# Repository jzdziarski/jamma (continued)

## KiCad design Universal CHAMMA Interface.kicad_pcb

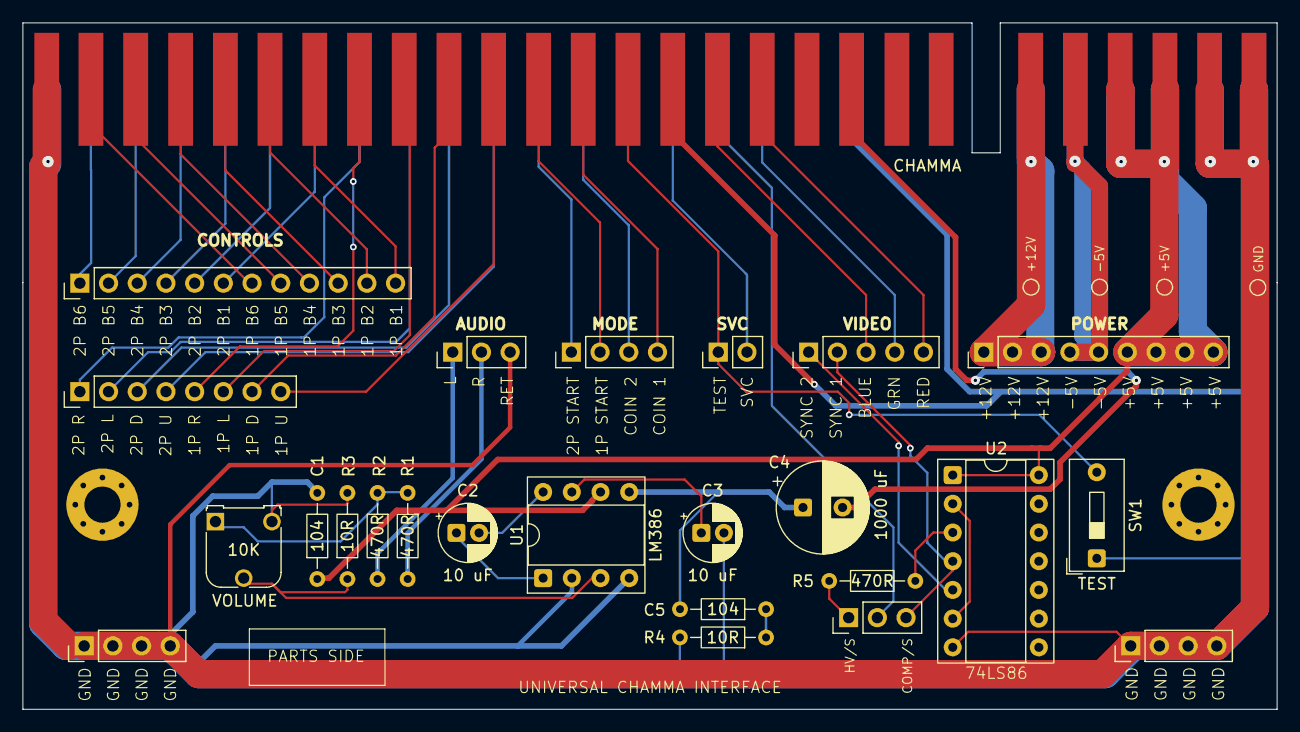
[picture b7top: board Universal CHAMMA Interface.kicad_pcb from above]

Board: 2 copper layers, 111.0 x 60.8 mm, 29 parts (0 on the bottom side), 49 nets.

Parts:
+5V, +12V: TestPoint_Pad_D1.0mm
-5V: TestPoint_Pad_D1.0mm
AUDIO: PinHeader_1x03_P2.54mm_Vertical
C1, C5: 104; R_Axial_DIN0204_L3.6mm_D1.6mm_P7.62mm_Horizontal
C2, C3: 10 uF; CP_Radial_D5.0mm_P2.00mm
C4: 1000 uF; CP_Radial_D8.0mm_P3.50mm
CHAMMA: HDR_JAMMA_56P_EDGE_CONNECTOR
CONTROLS: PinHeader_1x12_P2.54mm_Vertical
DIRECTIONALS: PinHeader_1x08_P2.54mm_Vertical
GND: TestPoint_Pad_D1.0mm
Ground: PinHeader_1x04_P2.54mm_Vertical
Ground#2: PinHeader_1x04_P2.54mm_Vertical
HV/S: PinHeader_1x03_P2.54mm_Vertical
MODE: PinHeader_1x04_P2.54mm_Vertical
POWER: PinHeader_1x09_P2.54mm_Vertical
R1, R2, R5: 470R; R_Axial_DIN0204_L3.6mm_D1.6mm_P7.62mm_Horizontal
R3, R4: 10R; R_Axial_DIN0204_L3.6mm_D1.6mm_P7.62mm_Horizontal
SVC: PinHeader_1x02_P2.54mm_Vertical
TEST: SW1; SW_DIP_SPSTx01_Slide_9.78x4.72mm_W7.62mm_P2.54mm
U1: LM386; DIP-8_W7.62mm_Socket
U2: DIP-14_W7.62mm_Socket
VIDEO: PinHeader_1x05_P2.54mm_Vertical
VOLUME: 10K; Potentiometer_Runtron_RM-065_Vertical

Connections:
1P_B1: CHAMMA.22, CONTROLS.12
1P_B2: CHAMMA.23, CONTROLS.11
1P_B3: CHAMMA.24, CONTROLS.10
1P_B4: CHAMMA.25, CONTROLS.9
1P_B5: CHAMMA.26, CONTROLS.8
1P_B6: CHAMMA.27, CONTROLS.7
1P_D: CHAMMA.19, DIRECTIONALS.7
1P_L: CHAMMA.20, DIRECTIONALS.6
1P_R: CHAMMA.21, DIRECTIONALS.5
1P_START: CHAMMA.17, MODE.2
1P_U: CHAMMA.18, DIRECTIONALS.8
2P_B1: CHAMMA.Z, CONTROLS.6
2P_B2: CHAMMA.a, CONTROLS.5
2P_B3: CHAMMA.b, CONTROLS.4
2P_B4: CHAMMA.c, CONTROLS.3
2P_B5: CHAMMA.d, CONTROLS.2
2P_B6: CHAMMA.e, CONTROLS.1
2P_D: CHAMMA.W, DIRECTIONALS.3
2P_L: CHAMMA.X, DIRECTIONALS.2
2P_R: CHAMMA.Y, DIRECTIONALS.1
2P_START: CHAMMA.U, MODE.1
2P_U: CHAMMA.V, DIRECTIONALS.4
+5V: +5V.1, C1.1, CHAMMA.3, CHAMMA.4, CHAMMA.C, CHAMMA.D, POWER.6, POWER.7, POWER.8, POWER.9, U1.6, U2.1, U2.14
+12V: +12V.1, CHAMMA.6, CHAMMA.F, POWER.1, POWER.2, POWER.3
-5V: -5V.1, CHAMMA.5, CHAMMA.E, POWER.4, POWER.5
AUDIO_L: AUDIO.1, R2.2
AUDIO_MONO: R1.1, R2.1, VOLUME.1
AUDIO_R: AUDIO.2, R1.2
C5_R4: C5.1, R4.1
COIN_1: CHAMMA.16, MODE.4
COIN_2: CHAMMA.T, MODE.3
GND: AUDIO.3, C1.2, C3.2, CHAMMA.1, CHAMMA.2, CHAMMA.14, CHAMMA.28, CHAMMA.A, CHAMMA.B, CHAMMA.L, CHAMMA.f, GND.1, Ground.1, Ground.2, Ground.3, Ground.4, Ground#2.1, Ground#2.2, Ground#2.3, Ground#2.4, R3.2, R4.2, TEST.1, U1.2, U1.4, U2.7, VOLUME.3
PREAMP: R3.1, U1.3, VOLUME.2
PREAMP_OUT: C4.1, C5.2, U1.5
SERVICE: CHAMMA.R, SVC.2
SPKR+: C4.2, CHAMMA.10
TEST: CHAMMA.15, SVC.1, TEST.2
U4_BYPASS: C3.1, U1.7
U4_GAIN_P1: C2.1, U1.1
U4_GAIN_P8: C2.2, U1.8
VID_B: CHAMMA.13, VIDEO.3
VID_CSYNC: CHAMMA.P, HV/S.2
VID_G: CHAMMA.N, VIDEO.4
VID_NXOR: HV/S.1, R5.1
VID_NXOR_R5: R5.2, U2.3
VID_R: CHAMMA.12, VIDEO.5
VID_SYN1: HV/S.3, U2.4, VIDEO.2
VID_SYN2: U2.5, VIDEO.1
VID_XOR: U2.2, U2.6

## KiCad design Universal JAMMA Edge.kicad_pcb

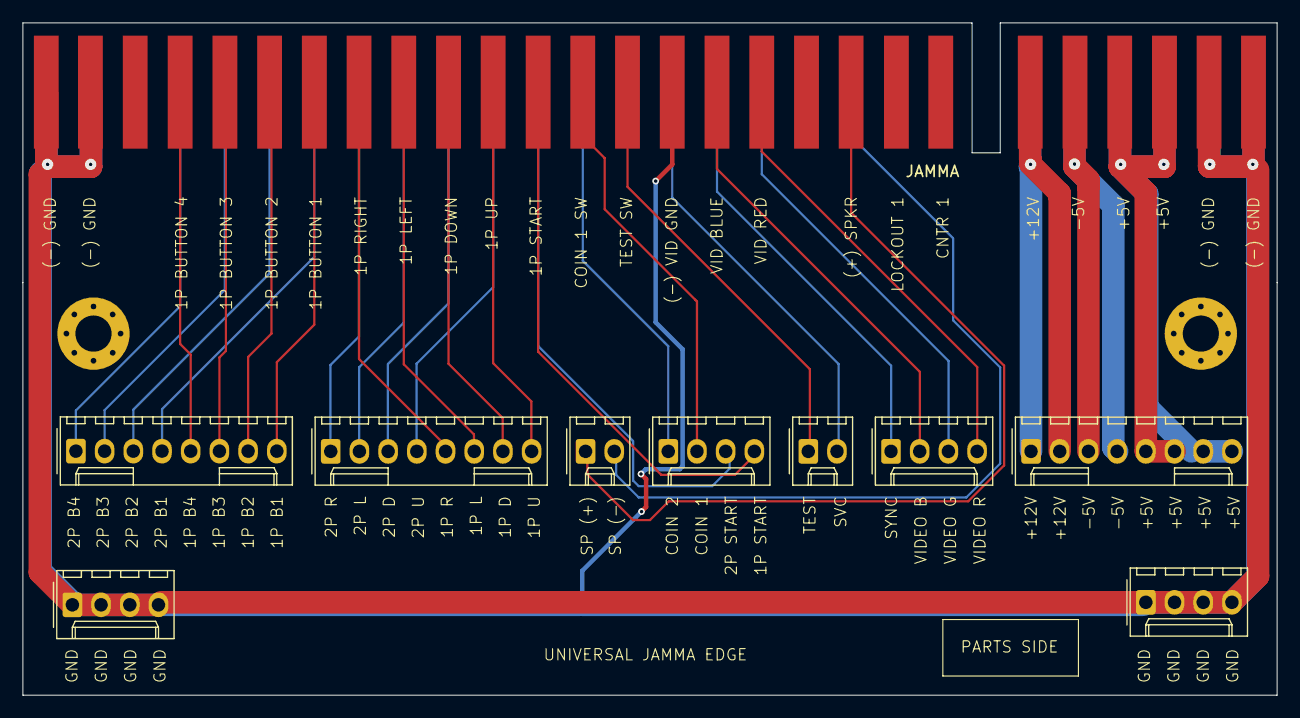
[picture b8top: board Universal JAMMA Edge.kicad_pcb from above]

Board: 2 copper layers, 111.0 x 59.5 mm, 4 parts (0 on the bottom side), 4 nets.

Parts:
Ground: Molex_KK-254_AE-6410-04A_1x04_P2.54mm_Vertical
Ground#2: Molex_KK-254_AE-6410-04A_1x04_P2.54mm_Vertical
JAMMA: HDR_JAMMA_56P_EDGE_CONNECTOR
Power: Molex_KK-254_AE-6410-08A_1x08_P2.54mm_Vertical

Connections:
+5V: JAMMA.3, JAMMA.4, JAMMA.C, JAMMA.D, Power.5, Power.6, Power.7, Power.8
+12V: JAMMA.6, JAMMA.F, Power.1, Power.2
-5V: JAMMA.5, JAMMA.E, Power.3, Power.4
GND: Ground.1, Ground.2, Ground.3, Ground.4, Ground#2.1, Ground#2.2, Ground#2.3, Ground#2.4, JAMMA.1, JAMMA.2, JAMMA.14, JAMMA.27, JAMMA.28, JAMMA.A, JAMMA.B, JAMMA.e, JAMMA.f
